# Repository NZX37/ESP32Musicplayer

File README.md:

# Mini Music Player

A rechargeable music player built around an ESP32-S3. The design is intended to play music stored on a microSD card and send stereo audio to standard headphones through a 3.5 mm jack. I made it to learn how the digital, audio, charging, PCB, and enclosure parts of a small portable device fit together.

## How it works

The ESP32-S3 is the central controller. It reads music data from the microSD socket and sends digital audio over I²S to a PCM5102 digital-to-analog converter. The analog stereo signal then passes through a TPA6132A2 headphone amplifier and out through the 3.5 mm headphone jack. A ST7789 TFT is included as the user display. A TP4056-based circuit handles single-cell Li-ion charging, and a boost converter provides the higher supply rail required by the audio section. The battery, display, card socket, audio parts, and connectors are placed on the custom PCB and fit into the two-piece printed enclosure.

The KiCad schematic is the wiring reference for this design. The connections are intended to be made by the PCB, rather than by a separate hand-wired harness. Review the schematic and component datasheets before ordering or powering a board; this design has not yet been documented as a verified working build.

## Design files and images

Open the KiCad project in `PCB/` to inspect or edit the schematic and board. `Minimusicplayer.step` is the 3D assembly export, while `Case/CASE.stl` and `Case/LID.stl` are the enclosure parts.

### Schematic

### PCB layout

### Enclosure model

The case and lid STL files are included. A photo of the physical build will be added after the device has been assembled.

## Bill of materials

Prices are the estimates recorded during design and may change by seller, region, and shipping. The total below sums the listed line items; it excludes shipping and does not include parts without a recorded price.

| Part | Qty. | Supplier | Unit price | Line total | Purchase link |
| --- | ---: | --- | ---: | ---: | --- |
| 2.25-inch ST7789 TFT LCD, 2.8–3.3 V | 1 | AliExpress | $6.05 | $6.05 | [Product listing](https://www.aliexpress.com/item/1005009266053584.html) |
| Waveshare ESP32-S3-WROOM-1-N8R8 | 1 | BerryBase / Waveshare | $16.88 | $16.88 | [Product page](https://www.berrybase.de/en/waveshare-esp32-s3-wroom-1-n8r8-microcontroller-aiot-wi-fi-bt-ble-240mhz-dual-core-without-header) |
| PCM5102 I²S DAC | 1 | Adafruit | $4.95 | $4.95 | [Product page](https://www.adafruit.com/product/6250) |
| DC-DC boost converter | 1 | Kuriosity | $4.40 | $4.40 | [Product page](https://kuriosity.sg/products/dc-dc-step-up-boost-converter-2-5-vout-to-5-12v-1a-5w) |
| SJ1-3535NG 3.5 mm stereo jack | 1 | DigiKey | $2.22 | $2.22 | [Product page](https://www.digikey.sg/en/products/detail/same-sky-formerly-cui-devices/SJ1-3535NG/738699) |
| Custom PCB | 1 | JLCPCB | $2.00 | $2.00 | [PCB service](https://jlcpcb.com) |
| PCB assembly (PCBA) | 1 | JLCPCB | $29.83 | $29.83 | [Assembly service](https://jlcpcb.com) |
| **Listed parts subtotal** |  |  |  | **$66.33** |  |

The schematic also contains a TP4056 charger, TPA6132A2 headphone amplifier, microSD socket, and other passives/connectors. Their individual purchase links and prices are not present in the current `BOM.csv`, so the subtotal is incomplete. Check `BOM.csv` for the source list and update it as these costs are confirmed.

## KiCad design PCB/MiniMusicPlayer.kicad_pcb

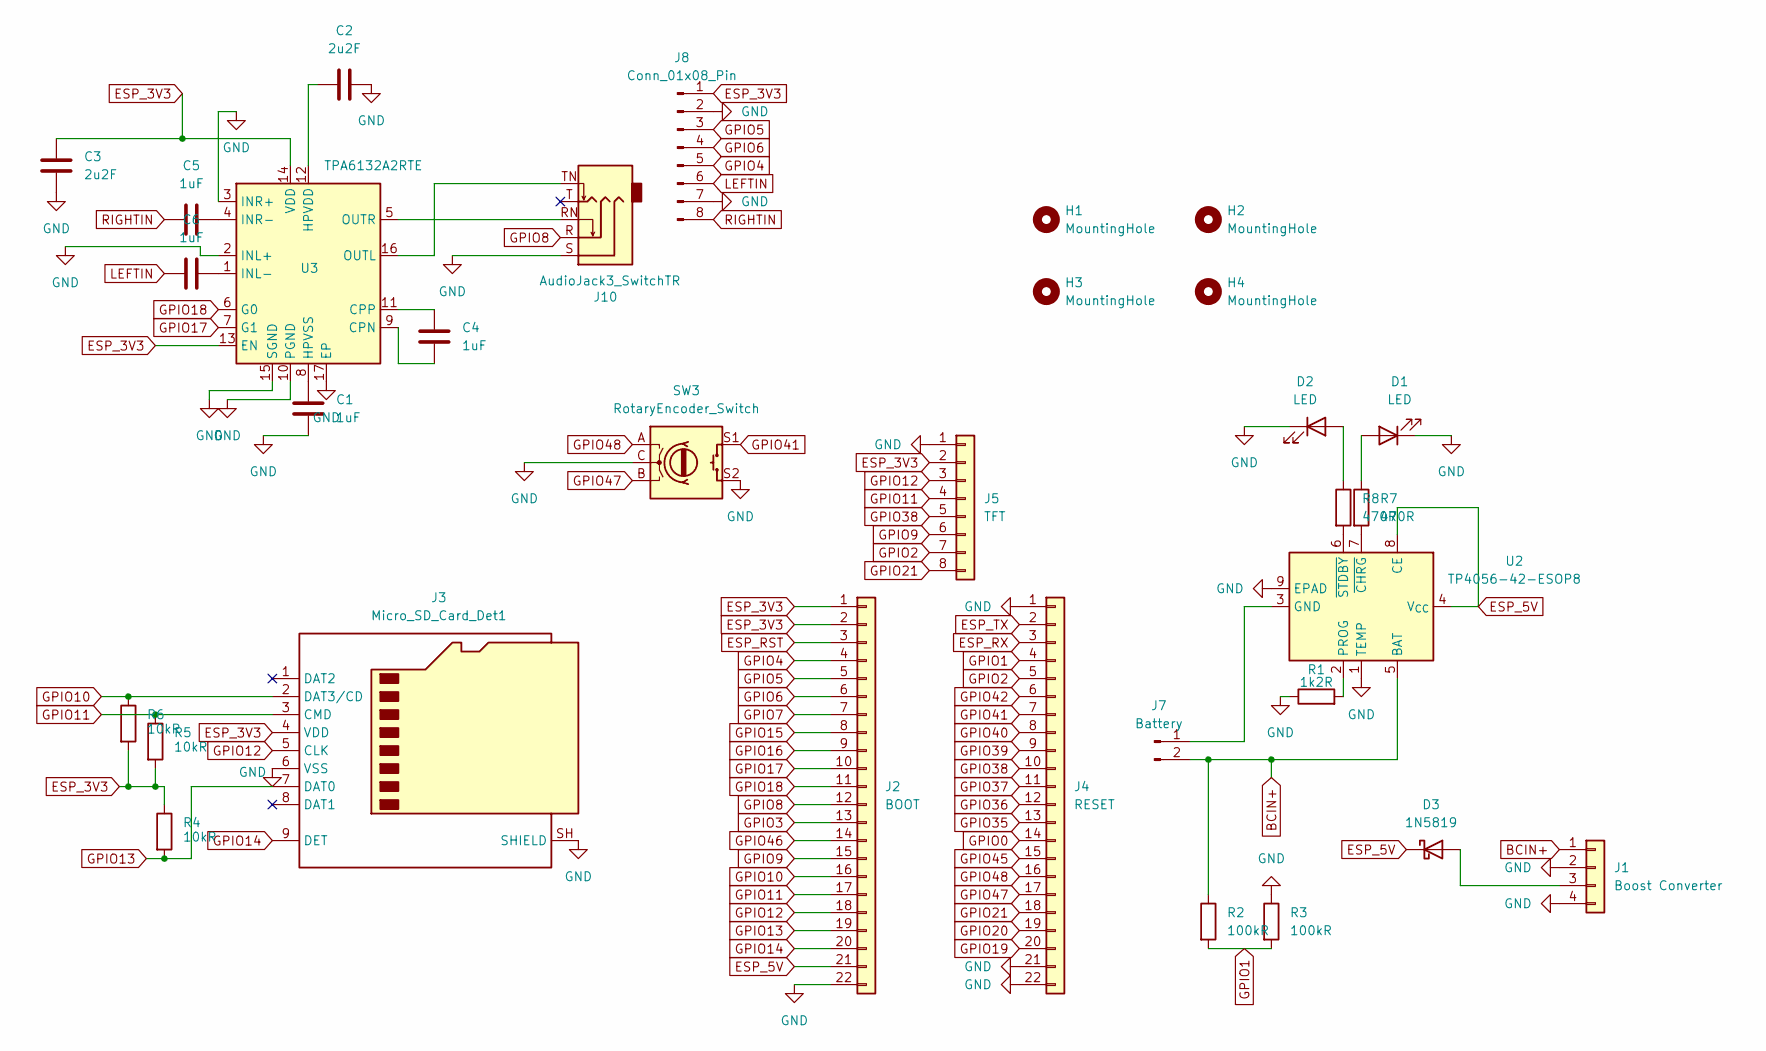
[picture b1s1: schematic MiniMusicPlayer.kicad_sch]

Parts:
C1, C4, C5, C6: 1uF; C_0805_2012Metric_Pad1.18x1.45mm_HandSolder
C2, C3: 2u2F; C_0805_2012Metric_Pad1.18x1.45mm_HandSolder
D1, D2: LED; LED_D3.0mm
D3: 1N5819; D_DO-41_SOD81_P10.16mm_Horizontal
H1, H2, H3, H4: MountingHole; MountingHole_3.2mm_M3
J1: Boost Converter; PinSocket_1x04_P2.54mm_Vertical
J2: BOOT; PinSocket_1x22_P2.54mm_Vertical
J3: Micro_SD_Card_Det1; microSD_HC_Molex_104031-0811
J4: RESET; PinSocket_1x22_P2.54mm_Vertical
J5: TFT; PinSocket_1x08_P2.54mm_Vertical
J7: Battery; PinHeader_1x02_P2.54mm_Vertical
J8: Conn_01x08_Pin; PinHeader_1x08_P2.54mm_Vertical
J10: AudioJack3_SwitchTR; Jack_3.5mm_CUI_SJ1-3535NG_Horizontal
R1: 1k2R; R_0805_2012Metric_Pad1.20x1.40mm_HandSolder
R2, R3: 100kR; R_0805_2012Metric_Pad1.20x1.40mm_HandSolder
R4, R5, R6: 10kR; R_0805_2012Metric_Pad1.20x1.40mm_HandSolder
R7, R8: 470R; R_0805_2012Metric_Pad1.20x1.40mm_HandSolder
SW3: RotaryEncoder_Switch; RotaryEncoder_Alps_EC12E-Switch_Vertical_H20mm
U2: TP4056-42-ESOP8; SOIC-8-1EP_3.9x4.9mm_P1.27mm_EP2.41x3.3mm_ThermalVias
U3: TPA6132A2RTE; WQFN-16-1EP_3x3mm_P0.5mm_EP1.6x1.6mm_ThermalVias

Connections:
BCIN+: J1.1, J7.2, R2.1, U2.5 (BAT)
ESP_3V3: C3.2, J2.1, J2.2, J3.4 (VDD), J5.2, J8.1, R4.1, R5.2, R6.2, U3.13 (EN), U3.14 (VDD)
ESP_5V: D3.1 (K), J2.21, U2.4 (V_{CC}), U2.8 (CE)
ESP_RST: J2.3
ESP_RX: J4.3
ESP_TX: J4.2
GND: C1.2, C2.2, C3.1, D1.1 (K), D2.1 (K), J1.2, J1.4, J2.22, J3.6 (VSS), J3.SH (SHIELD), J4.1, J4.21, J4.22, J5.1, J8.2, J8.7, J10.S, R1.1, R3.1, SW3.C, SW3.S2, U2.1 (TEMP), U2.9 (EPAD), U3.2 (INL+), U3.3 (INR+), U3.10 (PGND), U3.15 (SGND), U3.17 (EP)
GPIO0: J4.14
GPIO1: J4.4, R2.2, R3.2
GPIO2: J4.5, J5.7
GPIO3: J2.13
GPIO4: J2.4, J8.5
GPIO5: J2.5, J8.3
GPIO6: J2.6, J8.4
GPIO7: J2.7
GPIO8: J2.12, J10.R
GPIO9: J2.15, J5.6
GPIO10: J2.16, J3.2 (DAT3/CD), R6.1
GPIO11: J2.17, J3.3 (CMD), J5.4, R5.1
GPIO12: J2.18, J3.5 (CLK), J5.3
GPIO13: J2.19, J3.7 (DAT0), R4.2
GPIO14: J2.20, J3.9 (DET)
GPIO15: J2.8
GPIO16: J2.9
GPIO17: J2.10, U3.7 (G1)
GPIO18: J2.11, U3.6 (G0)
GPIO19: J4.20
GPIO20: J4.19
GPIO21: J4.18, J5.8
GPIO35: J4.13
GPIO36: J4.12
GPIO37: J4.11
GPIO38: J4.10, J5.5
GPIO39: J4.9
GPIO40: J4.8
GPIO41: J4.7, SW3.S1
GPIO42: J4.6
GPIO45: J4.15
GPIO46: J2.14
GPIO47: J4.17, SW3.B
GPIO48: J4.16, SW3.A
LEFTIN: C6.2, J8.6
unnamed: D1.2 (A), R7.1
unnamed: D2.2 (A), R8.1
unnamed: D3.2 (A), J1.3
unnamed: J7.1, U2.3 (GND)
unnamed: R1.2, U2.2 (PROG)
unnamed: R7.2, U2.7 (~CHRG)
unnamed: R8.2, U2.6 (~STDBY)
unnamed: C4.2, U3.9 (CPN)
unnamed: C4.1, U3.11 (CPP)
unnamed: C2.1, U3.12 (HPVDD)
unnamed: C1.1, U3.8 (HPVSS)
unnamed: C6.1, U3.1 (INL-)
unnamed: C5.1, U3.4 (INR-)
unnamed: J10.TN, U3.16 (OUTL)
unnamed: J10.RN, U3.5 (OUTR)
RIGHTIN: C5.2, J8.8

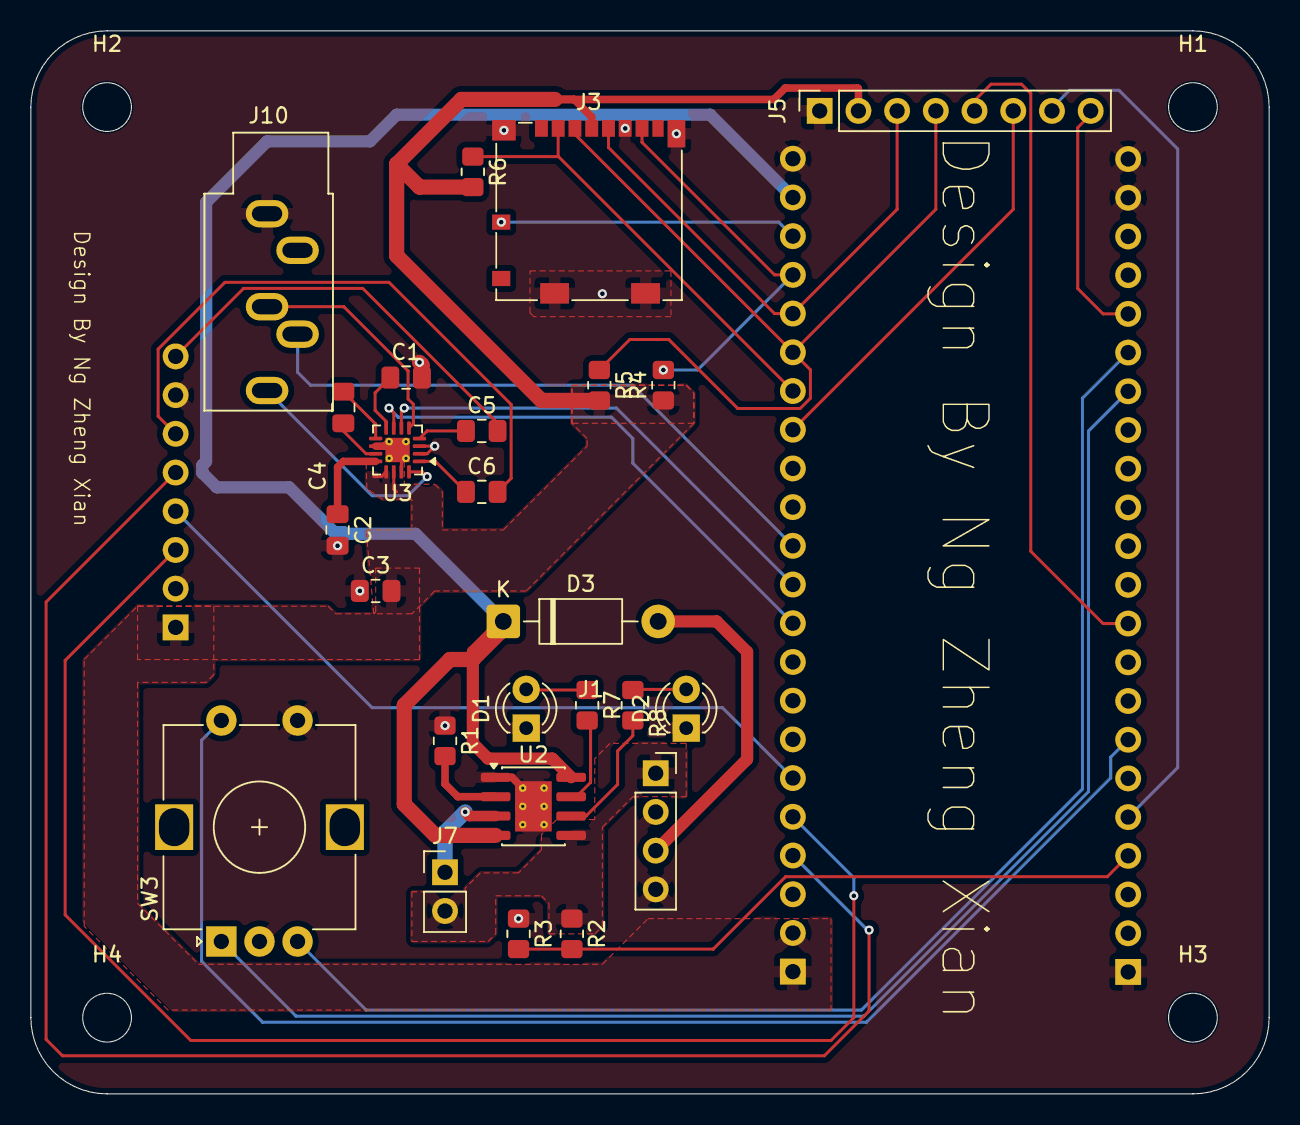
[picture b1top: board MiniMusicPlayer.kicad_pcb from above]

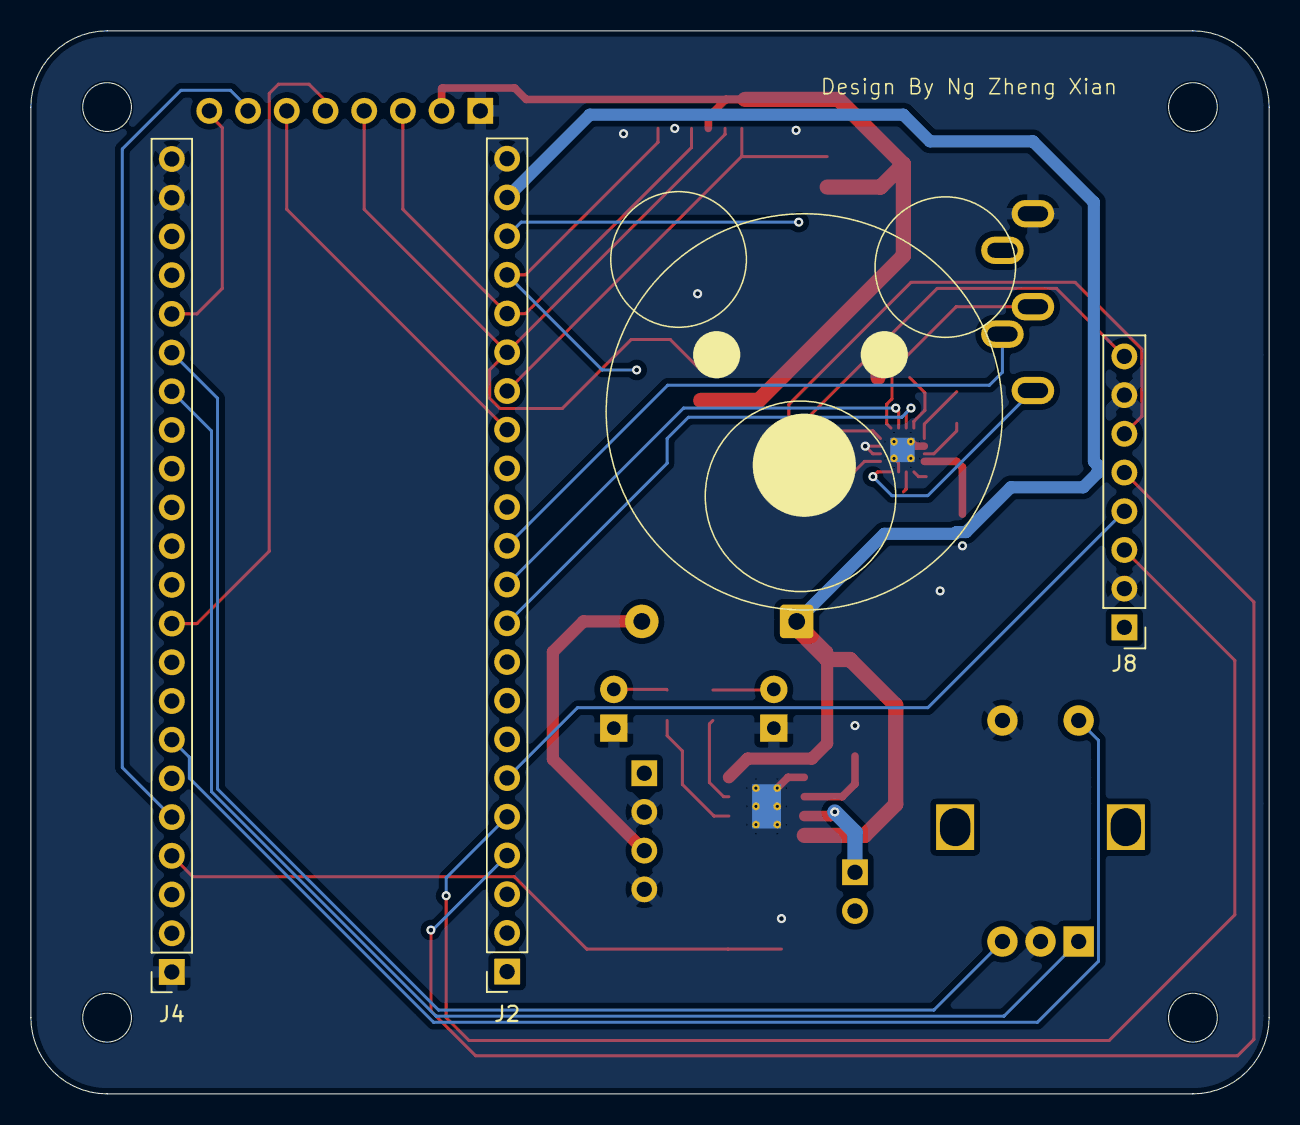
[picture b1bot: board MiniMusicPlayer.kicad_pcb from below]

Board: 2 copper layers, 81.2 x 69.8 mm, 32 parts (3 on the bottom side), 40 nets.
